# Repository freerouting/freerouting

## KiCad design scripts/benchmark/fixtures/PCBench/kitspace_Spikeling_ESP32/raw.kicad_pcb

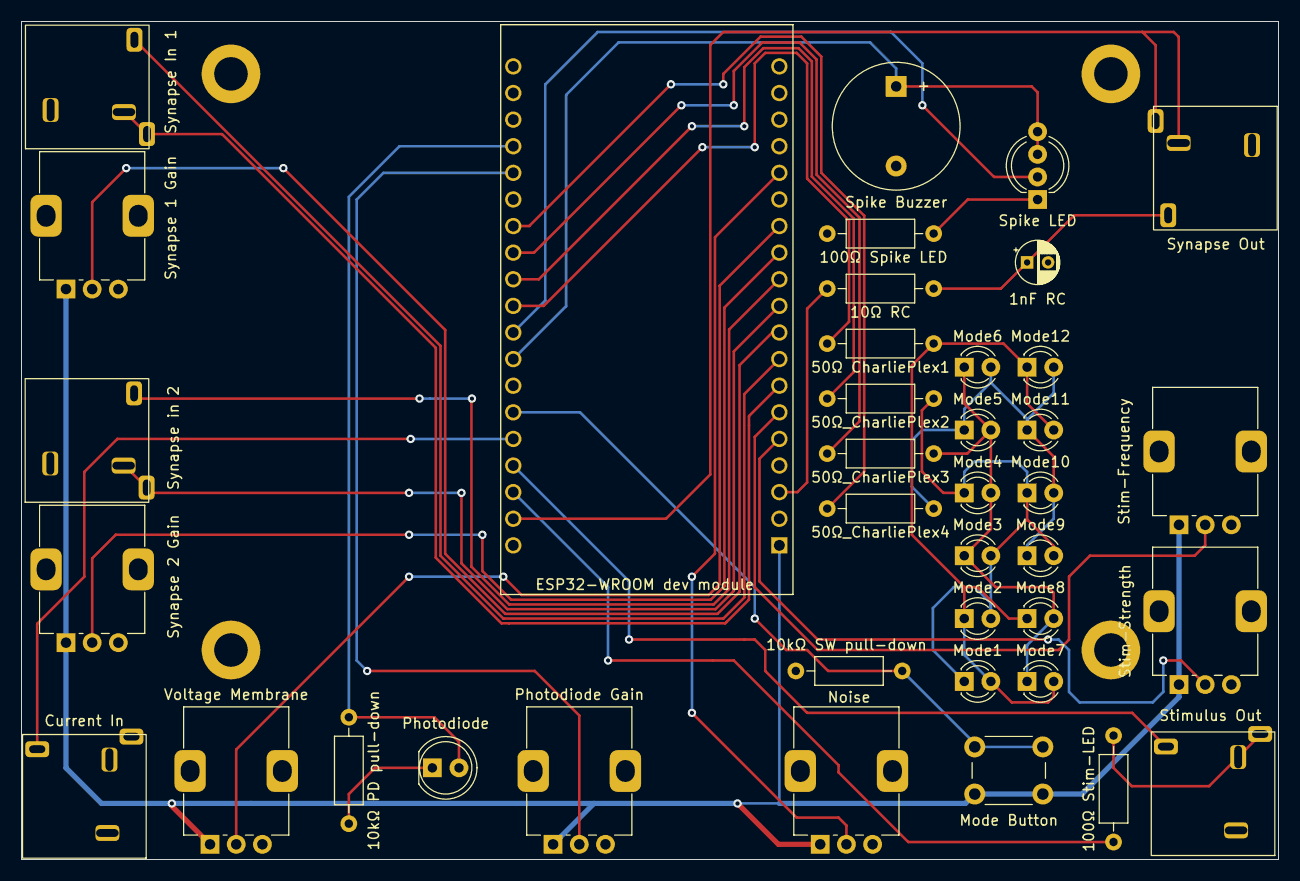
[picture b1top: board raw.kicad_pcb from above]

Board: 2 copper layers, 120.0 x 80.0 mm, 43 parts (0 on the bottom side), 33 nets.

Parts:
1nF RC: C1; CP_Radial_D4.0mm_P2.00mm
10kΩ PD pull-down: R2; R_Axial_DIN0207_L6.3mm_D2.5mm_P10.16mm_Horizontal
10kΩ SW pull-down: R5; R_Axial_DIN0207_L6.3mm_D2.5mm_P10.16mm_Horizontal
10Ω RC: R1; R_Axial_DIN0207_L6.3mm_D2.5mm_P10.16mm_Horizontal
50Ω CharliePlex1: R6; R_Axial_DIN0207_L6.3mm_D2.5mm_P10.16mm_Horizontal
50Ω_CharliePlex2: R7; R_Axial_DIN0207_L6.3mm_D2.5mm_P10.16mm_Horizontal
50Ω_CharliePlex3: R8; R_Axial_DIN0207_L6.3mm_D2.5mm_P10.16mm_Horizontal
50Ω_CharliePlex4: R9; R_Axial_DIN0207_L6.3mm_D2.5mm_P10.16mm_Horizontal
100Ω Spike LED: R4; R_Axial_DIN0207_L6.3mm_D2.5mm_P10.16mm_Horizontal
100Ω Stim-LED: R3; R_Axial_DIN0207_L6.3mm_D2.5mm_P10.16mm_Horizontal
 : MountingHole_3.2mm_M3_DIN965_Pad
 #2,  #3,  #4: MountingHole_3.2mm_M3_DIN965_Pad
Current In: J4; Audio Jack 3.5mm
ESP32-WROOM dev module: ESP32-DEVKITC-32D; MODULE_ESP32-DEVKITC-32D
Mode1: D2; LED_D3.0mm
Mode2: D3; LED_D3.0mm
Mode3: D4; LED_D3.0mm
Mode4: D5; LED_D3.0mm
Mode5: D6; LED_D3.0mm
Mode6: D7; LED_D3.0mm
Mode7: D8; LED_D3.0mm
Mode8: LED; LED_D3.0mm
Mode9: D10; LED_D3.0mm
Mode10: D11; LED_D3.0mm
Mode11: D12; LED_D3.0mm
Mode12: D13; LED_D3.0mm
Mode Button: SW1; SW_PUSH_6mm_H13mm
Noise: RV4; Potentiometer_Alps_RK09K_Single_Vertical
Photodiode: D1; LED_D5.0mm
Photodiode Gain: RV5; Potentiometer_Alps_RK09K_Single_Vertical
Spike Buzzer: BZ1; Buzzer_12x9.5RM7.6
Spike LED: RGB; LED_D5.0mm-4_RGB_Wide_Pins
Stim-Frequency: RV7; Potentiometer_Alps_RK09K_Single_Vertical
Stim-Strength: RV6; Potentiometer_Alps_RK09K_Single_Vertical
Stimulus Out: J5; Audio Jack 3.5mm
Synapse 1 Gain: RV1; Potentiometer_Alps_RK09K_Single_Vertical
Synapse 2 Gain: RV2; Potentiometer_Alps_RK09K_Single_Vertical
Synapse In 1: J2; Audio Jack 3.5mm
Synapse Out: J1; Audio Jack 3.5mm
Synapse in 2: J3; Audio Jack 3.5mm
Voltage Membrane: RV3; Potentiometer_Alps_RK09K_Single_Vertical

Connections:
+3V3: ESP32-WROOM dev module.1 (3V3), Mode Button.2, Noise.1, Photodiode Gain.1, Stim-Frequency.1, Stim-Strength.1, Synapse 1 Gain.1, Synapse 2 Gain.1, Voltage Membrane.1
/01: ESP32-WROOM dev module.23 (TXD0), Stimulus Out.R
/02: ESP32-WROOM dev module.34 (IO2), Photodiode Gain.2
/03: Current In.R, ESP32-WROOM dev module.24 (RXD0)
/04: 50Ω_CharliePlex4.1, ESP32-WROOM dev module.32 (IO4)
/05: 50Ω CharliePlex1.1, ESP32-WROOM dev module.29 (IO5)
/12: ESP32-WROOM dev module.13 (IO12), Voltage Membrane.2
/13: ESP32-WROOM dev module.15 (IO13), Noise.2
/14: ESP32-WROOM dev module.12 (IO14), Synapse 2 Gain.2
/15: 10kΩ PD pull-down.1, ESP32-WROOM dev module.35 (IO15), Photodiode.2 (A)
/16: 50Ω_CharliePlex3.1, ESP32-WROOM dev module.31 (IO16)
/17: 50Ω_CharliePlex2.1, ESP32-WROOM dev module.30 (IO17)
/18: ESP32-WROOM dev module.28 (IO18), Spike LED.2 (RA)
/19: ESP32-WROOM dev module.27 (IO19), Spike Buzzer.1 (-), Spike LED.3 (GA), Spike LED.4 (BA)
/21: 10kΩ SW pull-down.1, ESP32-WROOM dev module.25 (IO21), Mode Button.1
/22: 100Ω Stim-LED.1, ESP32-WROOM dev module.22 (IO22)
/23: ESP32-WROOM dev module.21 (IO23), Synapse Out.T
/25: ESP32-WROOM dev module.9 (IO25), Synapse 1 Gain.2
/26: ESP32-WROOM dev module.10 (IO26), Synapse in 2.T
/27: ESP32-WROOM dev module.11 (IO27), Synapse in 2.R
/32: ESP32-WROOM dev module.7 (IO32), Synapse In 1.T
/33: ESP32-WROOM dev module.8 (IO33), Synapse In 1.R
/34: ESP32-WROOM dev module.5 (IO34), Stim-Strength.2
/35: ESP32-WROOM dev module.6 (IO35), Stim-Frequency.2
/36: 10Ω RC.1, ESP32-WROOM dev module.3 (SENSOR_VP)
GNDREF: 1nF RC.2, 10kΩ PD pull-down.2, 10kΩ SW pull-down.2, 100Ω Spike LED.1, Current In.S, ESP32-WROOM dev module.14 (GND1), ESP32-WROOM dev module.20 (GND3), ESP32-WROOM dev module.26 (GND2), Noise.3, Photodiode.1 (K), Photodiode Gain.3, Spike Buzzer.2 (+), Stim-Frequency.3, Stim-Strength.3, Stimulus Out.S, Synapse 1 Gain.3, Synapse 2 Gain.3, Synapse In 1.S, Synapse Out.S, Synapse in 2.S, Voltage Membrane.3
unnamed: 1nF RC.1, 10Ω RC.2, Synapse Out.R
unnamed: 50Ω CharliePlex1.2, Mode1.2 (A), Mode2.1 (K), Mode7.2 (A), Mode8.1 (K), Mode11.2 (A), Mode12.1 (K)
unnamed: 50Ω_CharliePlex2.2, Mode1.1 (K), Mode2.2 (A), Mode3.2 (A), Mode4.1 (K), Mode9.2 (A), Mode10.1 (K)
unnamed: 50Ω_CharliePlex3.2, Mode3.1 (K), Mode4.2 (A), Mode5.2 (A), Mode6.1 (K), Mode7.1 (K), Mode8.2 (A)
unnamed: 50Ω_CharliePlex4.2, Mode5.1 (K), Mode6.2 (A), Mode9.1 (K), Mode10.2 (A), Mode11.1 (K), Mode12.2 (A)
unnamed: 100Ω Spike LED.2, Spike LED.1 (K)
unnamed: 100Ω Stim-LED.2, Stimulus Out.T

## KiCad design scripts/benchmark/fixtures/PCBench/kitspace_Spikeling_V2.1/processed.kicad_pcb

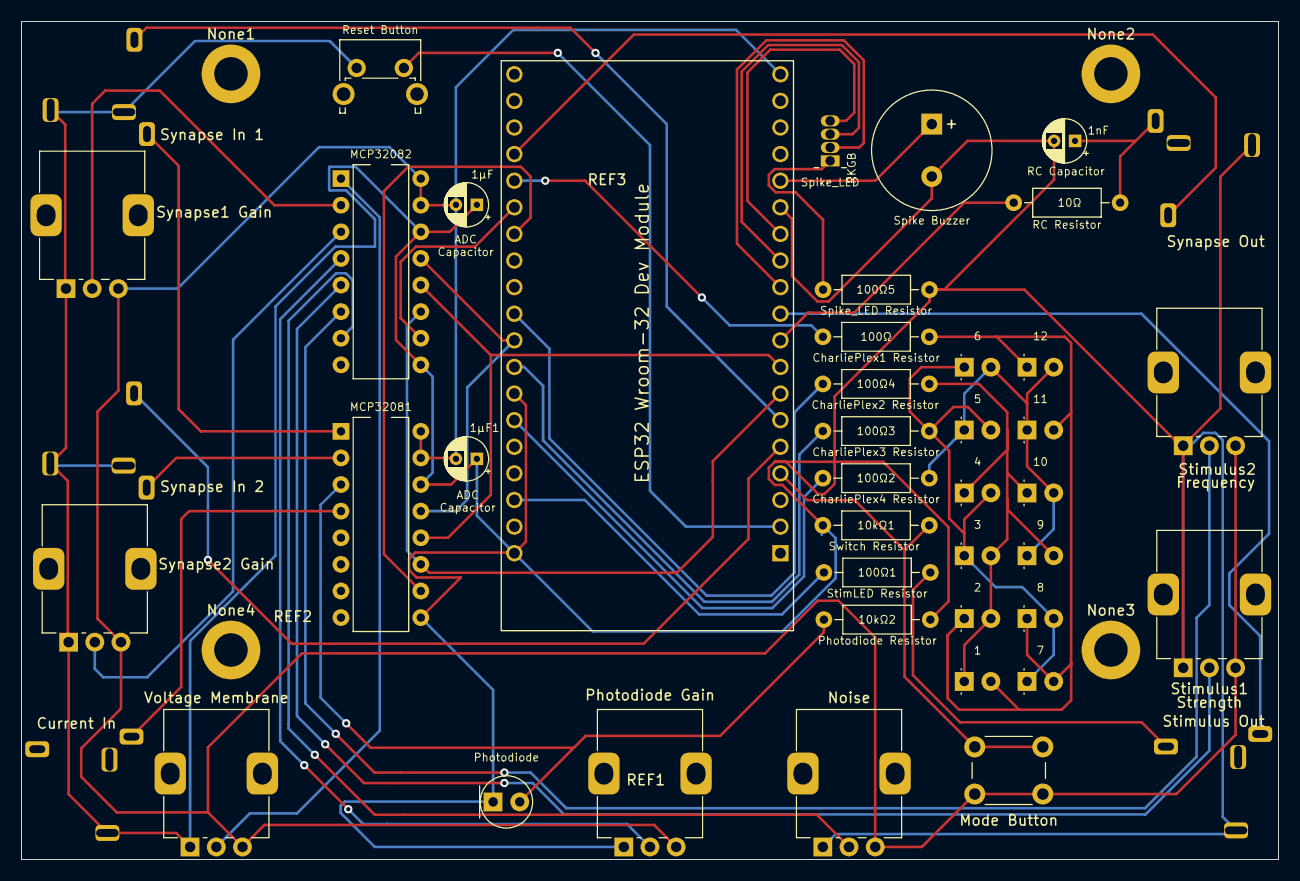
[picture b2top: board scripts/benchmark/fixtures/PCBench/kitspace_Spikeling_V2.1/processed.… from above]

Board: 2 copper layers, 120.0 x 80.0 mm, 51 parts (0 on the bottom side), 41 nets.

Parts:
1: D2; LED_D3.0mm
1nF: C3; CP_Radial_D4.0mm_P2.00mm
1μF, 1μF1: 1 μF; CP_Radial_D4.0mm_P2.00mm
2: D3; LED_D3.0mm
3: D4; LED_D3.0mm
4: D5; LED_D3.0mm
5: D6; LED_D3.0mm
6: D7; LED_D3.0mm
7: D8; LED_D3.0mm
8: LED; LED_D3.0mm
9: D10; LED_D3.0mm
10: D11; LED_D3.0mm
10kΩ1: R5; R_Axial_DIN0207_L6.3mm_D2.5mm_P10.16mm_Horizontal
10kΩ2: R2; R_Axial_DIN0207_L6.3mm_D2.5mm_P10.16mm_Horizontal
10Ω: R1; R_Axial_DIN0207_L6.3mm_D2.5mm_P10.16mm_Horizontal
11: D12; LED_D3.0mm
12: D13; LED_D3.0mm
100Ω: R6; R_Axial_DIN0207_L6.3mm_D2.5mm_P10.16mm_Horizontal
100Ω1: R3; R_Axial_DIN0207_L6.3mm_D2.5mm_P10.16mm_Horizontal
100Ω2: R9; R_Axial_DIN0207_L6.3mm_D2.5mm_P10.16mm_Horizontal
100Ω3: R8; R_Axial_DIN0207_L6.3mm_D2.5mm_P10.16mm_Horizontal
100Ω4: R7; R_Axial_DIN0207_L6.3mm_D2.5mm_P10.16mm_Horizontal
100Ω5: R4; R_Axial_DIN0207_L6.3mm_D2.5mm_P10.16mm_Horizontal
Current In: J4; Spikeling Audio Jack 3.5mm
ESP32 Wroom-32 Dev Module: ESP32-DEVKITC-32D; MODULE_ESP32-DEVKITC-32D
MCP32081: MCP32082; DIP-16_W7.62mm
MCP32082: MCP32084; DIP-16_W7.62mm
Mode Button: SW1; SW_PUSH_6mm_H13mm
Noise: RV4; Spikeling Potentiometer
None1, None3, None4: MountingHole_3.2mm_M3_DIN965_Pad
None2: MountingHole_M3; MountingHole_3.2mm_M3_DIN965_Pad
Photodiode: D1; LED_D5.0mm
Photodiode Gain: RV5; Spikeling Potentiometer
REF1: Spikeling_neuron; Spikeling_Photoreceptor
REF2: Spikeling_neuron; Spikeling_Electrode
REF3: Spikeling_neuron; Spikeling_Neuron
Reset Button: SW2; Spikeling reset button
Spike Buzzer: BZ1; Buzzer_11.5x9.5RM5
Spike_LED: RGB; LED_D5.0mm-4_RGB
Stimulus1: RV6; Spikeling Potentiometer
Stimulus2: RV7; Spikeling Potentiometer
Stimulus Out: J5; Spikeling Audio Jack 3.5mm
Synapse1 Gain: RV1; Spikeling Potentiometer
Synapse2 Gain: RV2; Spikeling Potentiometer
Synapse In 1: J2; Spikeling Audio Jack 3.5mm
Synapse In 2: J3; Spikeling Audio Jack 3.5mm
Synapse Out: J1; Spikeling Audio Jack 3.5mm
Voltage Membrane: RV3; Spikeling Potentiometer

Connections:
/00: ESP32 Wroom-32 Dev Module.33, MCP32082.10
/02: 100Ω.1, ESP32 Wroom-32 Dev Module.34
/04: ESP32 Wroom-32 Dev Module.32, MCP32081.10
/05: 100Ω4.1, ESP32 Wroom-32 Dev Module.29
/12: ESP32 Wroom-32 Dev Module.13, Spike_LED.4
/13: ESP32 Wroom-32 Dev Module.15, Spike Buzzer.1
/14: ESP32 Wroom-32 Dev Module.12, Spike_LED.3
/15: ESP32 Wroom-32 Dev Module.35, Synapse Out.T
/18: ESP32 Wroom-32 Dev Module.28, MCP32081.13, MCP32082.13
/19: 100Ω3.1, ESP32 Wroom-32 Dev Module.27
/21: 100Ω2.1, ESP32 Wroom-32 Dev Module.25
/22: 100Ω1.1, ESP32 Wroom-32 Dev Module.22
/25: 10Ω.1, ESP32 Wroom-32 Dev Module.9
/26: ESP32 Wroom-32 Dev Module.10, Stimulus Out.R
/27: ESP32 Wroom-32 Dev Module.11, Spike_LED.1
/32: ESP32 Wroom-32 Dev Module.7, MCP32081.11, MCP32082.11
/33: ESP32 Wroom-32 Dev Module.8, MCP32081.12, MCP32082.12
/34: ESP32 Wroom-32 Dev Module.5, Synapse In 2.T
/35: ESP32 Wroom-32 Dev Module.6, Synapse In 1.T
/39: 10kΩ1.1, ESP32 Wroom-32 Dev Module.4, Mode Button.1
/100: MCP32082.1, Voltage Membrane.2
/101: MCP32082.2, Synapse1 Gain.2
/102: MCP32082.3, Synapse2 Gain.2
/103: MCP32082.4, Photodiode Gain.2
/104: MCP32082.5, Stimulus1.2
/105: MCP32082.6, Stimulus2.2
/106: MCP32082.7, Noise.2
/200: MCP32081.1, Synapse In 1.R
/201: MCP32081.2, Synapse In 2.R
/202: 10kΩ2.1, MCP32081.3, Photodiode.2
/203: Current In.R, MCP32081.4
GNDREF: 1nF.2, 1μF.1, 1μF1.1, 10kΩ1.2, 10kΩ2.2, 100Ω5.1, Current In.S, ESP32 Wroom-32 Dev Module.14, ESP32 Wroom-32 Dev Module.20, ESP32 Wroom-32 Dev Module.26, MCP32081.9, MCP32081.14, MCP32082.9, MCP32082.14, Noise.1, Photodiode.1, Photodiode Gain.1, Reset Button.1, Spike Buzzer.2, Stimulus1.1, Stimulus2.1, Stimulus Out.S, Synapse1 Gain.1, Synapse2 Gain.1, Synapse In 1.S, Synapse In 2.S, Synapse Out.S, Voltage Membrane.1
unnamed: 1nF.1, 10Ω.2, Synapse Out.R
unnamed: 1.2, 2.1, 7.2, 8.1, 11.2, 12.1, 100Ω.2
unnamed: 1.1, 2.2, 3.2, 4.1, 9.2, 10.1, 100Ω4.2
unnamed: 3.1, 4.2, 5.2, 6.1, 7.1, 8.2, 100Ω3.2
unnamed: 5.1, 6.2, 9.1, 10.2, 11.1, 12.2, 100Ω2.2
unnamed: 100Ω5.2, Spike_LED.2
unnamed: 100Ω1.2, Stimulus Out.T
unnamed: ESP32 Wroom-32 Dev Module.2, Reset Button.2
VCC: 1μF.2, 1μF1.2, ESP32 Wroom-32 Dev Module.19, MCP32081.15, MCP32081.16, MCP32082.15, MCP32082.16, Mode Button.2, Noise.3, Photodiode Gain.3, Stimulus1.3, Stimulus2.3, Synapse1 Gain.3, Synapse2 Gain.3, Voltage Membrane.3

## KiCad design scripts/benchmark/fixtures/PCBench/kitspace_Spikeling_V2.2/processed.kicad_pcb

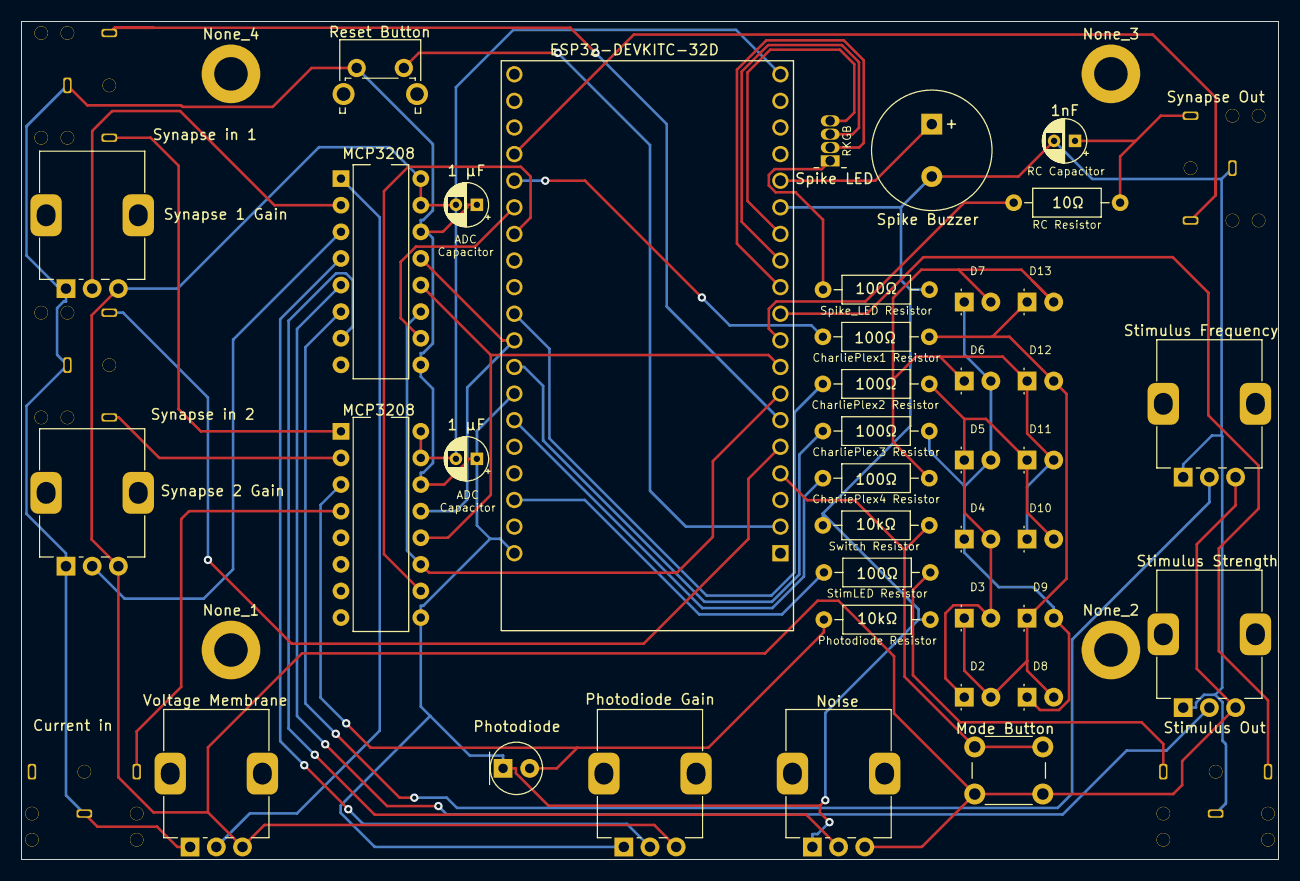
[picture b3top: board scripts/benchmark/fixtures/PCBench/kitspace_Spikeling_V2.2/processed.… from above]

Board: 2 copper layers, 120.0 x 80.0 mm, 48 parts (0 on the bottom side), 41 nets.

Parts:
BZ1: Spike Buzzer; Buzzer_11.5x9.5RM5
C1, C2: 1 μF; CP_Radial_D4.0mm_P2.00mm
C3: 1nF; CP_Radial_D4.0mm_P2.00mm
D1: Photodiode; LED_D5.0mm
D2: Mode1; LED_D3.0mm
D3: Mode2; LED_D3.0mm
D4: Mode3; LED_D3.0mm
D5: Mode4; LED_D3.0mm
D6: Mode5; LED_D3.0mm
D7: Mode6; LED_D3.0mm
D8: Mode7; LED_D3.0mm
D9: Mode8; LED_D3.0mm
D10: Mode9; LED_D3.0mm
D11: Mode10; LED_D3.0mm
D12: Mode11; LED_D3.0mm
D13: Mode12; LED_D3.0mm
D14: Spike LED; LED_D5.0mm-4_RGB
J1: Synapse Out; Spikeling Audio Jack 3.5mm
J2: Synapse in 1; Spikeling Audio Jack 3.5mm
J3: Synapse in 2; Spikeling Audio Jack 3.5mm
J4: Current in; Spikeling Audio Jack 3.5mm
J5: Stimulus Out; Spikeling Audio Jack 3.5mm
None_1, None_2, None_4: MountingHole_3.2mm_M3_DIN965_Pad
None_3: MountingHole_M3; MountingHole_3.2mm_M3_DIN965_Pad
R1: 10Ω; R_Axial_DIN0207_L6.3mm_D2.5mm_P10.16mm_Horizontal
R2, R5: 10kΩ; R_Axial_DIN0207_L6.3mm_D2.5mm_P10.16mm_Horizontal
R3, R4, R6, R7, R8, R9: 100Ω; R_Axial_DIN0207_L6.3mm_D2.5mm_P10.16mm_Horizontal
RV1: Synapse 1 Gain; Spikeling Potentiometer
RV2: Synapse 2 Gain; Spikeling Potentiometer
RV3: Voltage Membrane; Spikeling Potentiometer
RV4: Noise; Spikeling Potentiometer
RV5: Photodiode Gain; Spikeling Potentiometer
RV6: Stimulus Strength; Spikeling Potentiometer
RV7: Stimulus Frequency; Spikeling Potentiometer
SW1: Mode Button; SW_PUSH_6mm_H13mm
SW2: Reset Button; Spikeling reset button
U1: ESP32-DEVKITC-32D; MODULE_ESP32-DEVKITC-32D
U2, U3: MCP3208; DIP-16_W7.62mm

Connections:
/00: U1.33, U2.10
/02: R6.1, U1.34
/04: U1.32, U3.10
/05: R7.1, U1.29
/12: D14.4, U1.13
/13: BZ1.1, U1.15
/14: D14.3, U1.12
/15: J1.T, U1.35
/18: U1.28, U2.13, U3.13
/19: R8.1, U1.27
/21: R9.1, U1.25
/22: R3.1, U1.22
/25: R1.1, U1.9
/26: J5.R, U1.10
/27: D14.1, U1.11
/32: U1.7, U2.11, U3.11
/33: U1.8, U2.12, U3.12
/34: J3.T, U1.5
/35: J2.T, U1.6
/39: R5.1, SW1.1, U1.4
/100: RV3.2, U2.1
/101: RV1.2, U2.2
/102: RV2.2, U2.3
/103: RV5.2, U2.4
/104: RV6.2, U2.5
/105: RV7.2, U2.6
/106: RV4.2, U2.7
/200: J2.R, U3.1
/201: J3.R, U3.2
/202: D1.2, R2.1, U3.3
/203: J4.R, U3.4
GNDREF: BZ1.2, C1.1, C2.1, C3.2, D1.1, J1.S, J2.S, J3.S, J4.S, J5.S, R2.2, R4.1, R5.2, RV1.1, RV2.1, RV3.1, RV4.1, RV5.1, RV6.1, RV7.1, SW2.1, U1.14, U1.20, U1.26, U2.9, U2.14, U3.9, U3.14
unnamed: C3.1, J1.R, R1.2
unnamed: J5.T, R3.2
unnamed: D14.2, R4.2
unnamed: D2.2, D3.1, D8.2, D9.1, D12.2, D13.1, R6.2
unnamed: D2.1, D3.2, D4.2, D5.1, D10.2, D11.1, R7.2
unnamed: D4.1, D5.2, D6.2, D7.1, D8.1, D9.2, R8.2
unnamed: D6.1, D7.2, D10.1, D11.2, D12.1, D13.2, R9.2
unnamed: SW2.2, U1.2
VCC: C1.2, C2.2, RV1.3, RV2.3, RV3.3, RV4.3, RV5.3, RV6.3, RV7.3, SW1.2, U1.19, U2.15, U2.16, U3.15, U3.16
